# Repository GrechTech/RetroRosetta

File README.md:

# RetroRosetta

Check the Wiki page for more information
https://github.com/GrechTech/RetroRosetta/wiki

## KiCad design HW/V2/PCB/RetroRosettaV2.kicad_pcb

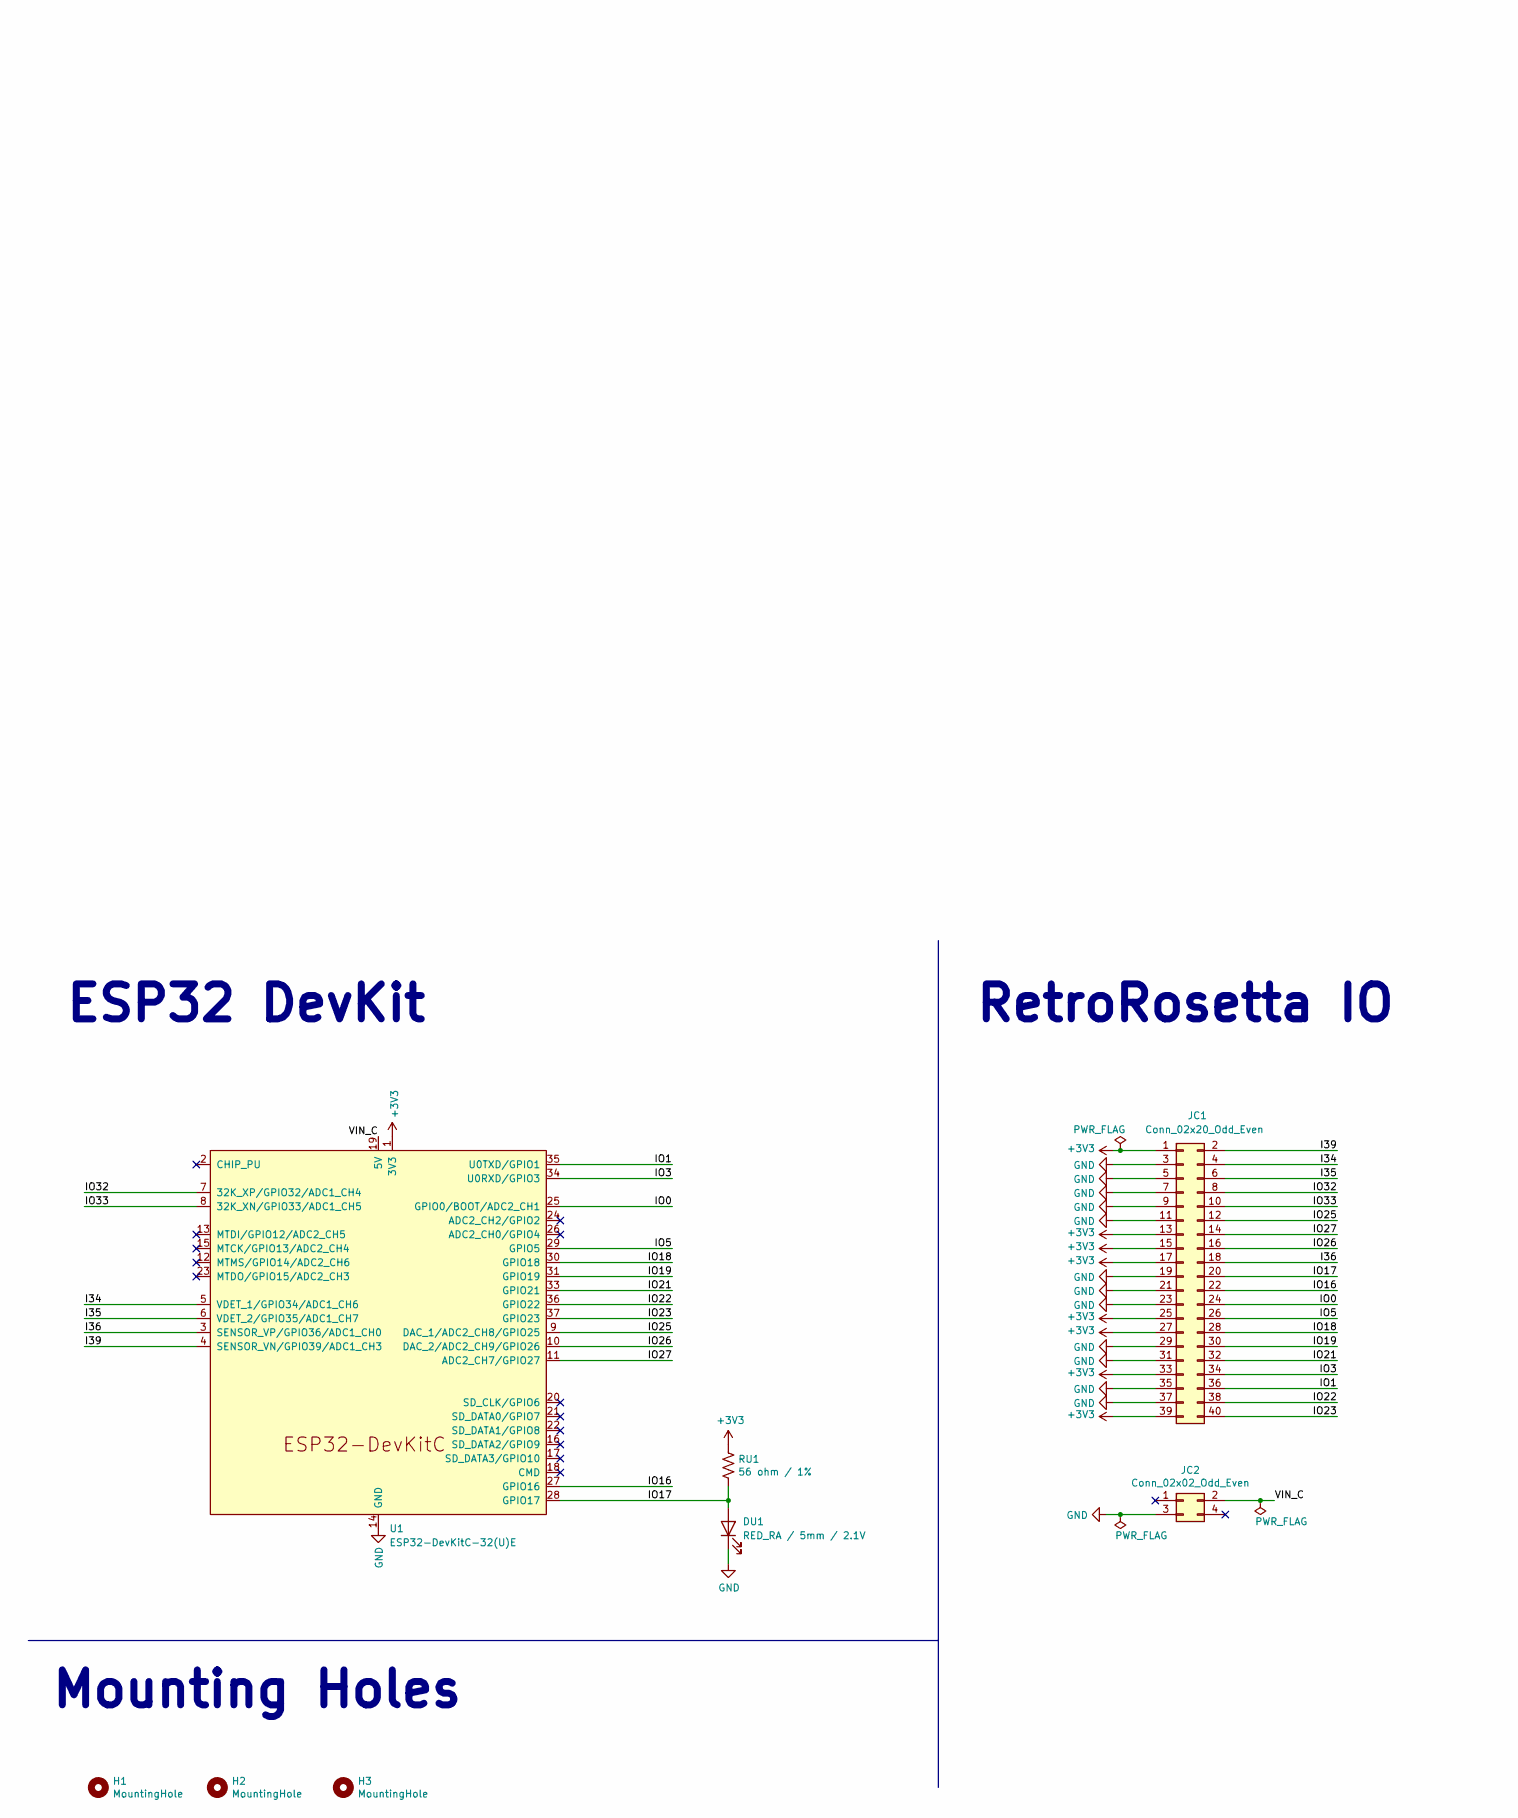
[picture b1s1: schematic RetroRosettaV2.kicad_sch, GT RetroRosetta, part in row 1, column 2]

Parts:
DU1: RED_RA / 5mm / 2.1V; LED_D5.0mm; Manufacturer_Part_Number C503B-RAN-CZ0C0AA2; DigiKey Part Number C503B-RAN-CZ0C0AA2CT-ND
H1, H2, H3: MountingHole; MountingHole_2.2mm_M2; Manufacturer_Part_Number DNP; DigiKey Part Number DNP
JC1: Conn_02x20_Odd_Even; PinHeader_2x20_P2.54mm_Vertical; Manufacturer_Part_Number Male 2.54mm pin header 2x20; DigiKey Part Number Male 2.54mm pin header 2x20
JC2: Conn_02x02_Odd_Even; PinHeader_2x02_P2.54mm_Vertical; Manufacturer_Part_Number Male 2.54mm pin header 2x2; DigiKey Part Number Male 2.54mm pin header 2x2
RU1: 56 ohm / 1%; R_Axial_DIN0204_L3.6mm_D1.6mm_P7.62mm_Horizontal; Manufacturer_Part_Number MFR-25FTE52-56R; DigiKey Part Number 13-MFR-25FTE52-56RCT-ND
U1: ESP32-DevKitC-32(U)E; ESP32-DevKitC; Manufacturer_Part_Number ESP32-DEVKITC-32E; DigiKey Part Number 1965-ESP32-DEVKITC-32E-ND

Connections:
+3V3: JC1.1, JC1.13, JC1.15, JC1.17, JC1.25, JC1.27, JC1.33, JC1.39, RU1.1, U1.1 (3V3)
/I34: JC1.4, U1.5 (VDET_1/GPIO34/ADC1_CH6)
/I35: JC1.6, U1.6 (VDET_2/GPIO35/ADC1_CH7)
/I36: JC1.18, U1.3 (SENSOR_VP/GPIO36/ADC1_CH0)
/I39: JC1.2, U1.4 (SENSOR_VN/GPIO39/ADC1_CH3)
/IO0: JC1.24, U1.25 (GPIO0/BOOT/ADC2_CH1)
/IO1: JC1.36, U1.35 (U0TXD/GPIO1)
/IO3: JC1.34, U1.34 (U0RXD/GPIO3)
/IO5: JC1.26, U1.29 (GPIO5)
/IO16: JC1.22, U1.27 (GPIO16)
/IO17: DU1.2 (A), JC1.20, RU1.2, U1.28 (GPIO17)
/IO18: JC1.28, U1.30 (GPIO18)
/IO19: JC1.30, U1.31 (GPIO19)
/IO21: JC1.32, U1.33 (GPIO21)
/IO22: JC1.38, U1.36 (GPIO22)
/IO23: JC1.40, U1.37 (GPIO23)
/IO25: JC1.12, U1.9 (DAC_1/ADC2_CH8/GPIO25)
/IO26: JC1.16, U1.10 (DAC_2/ADC2_CH9/GPIO26)
/IO27: JC1.14, U1.11 (ADC2_CH7/GPIO27)
/IO32: JC1.8, U1.7 (32K_XP/GPIO32/ADC1_CH4)
/IO33: JC1.10, U1.8 (32K_XN/GPIO33/ADC1_CH5)
/VIN_C: JC2.2, U1.19 (5V)
GND: DU1.1 (K), JC1.3, JC1.5, JC1.7, JC1.9, JC1.11, JC1.19, JC1.21, JC1.23, JC1.29, JC1.31, JC1.35, JC1.37, JC2.3, U1.14 (GND), U1.32 (GND), U1.38 (GND)

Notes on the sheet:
Mounting Holes
ESP32 DevKit
RetroRosetta IO

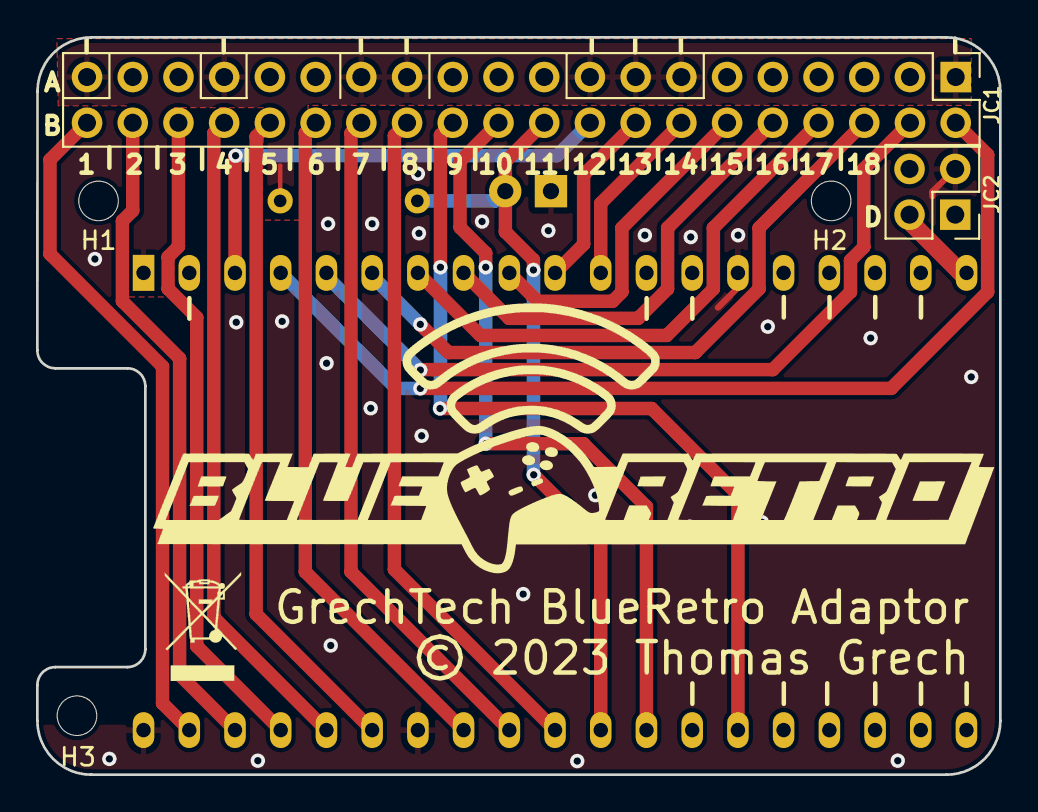
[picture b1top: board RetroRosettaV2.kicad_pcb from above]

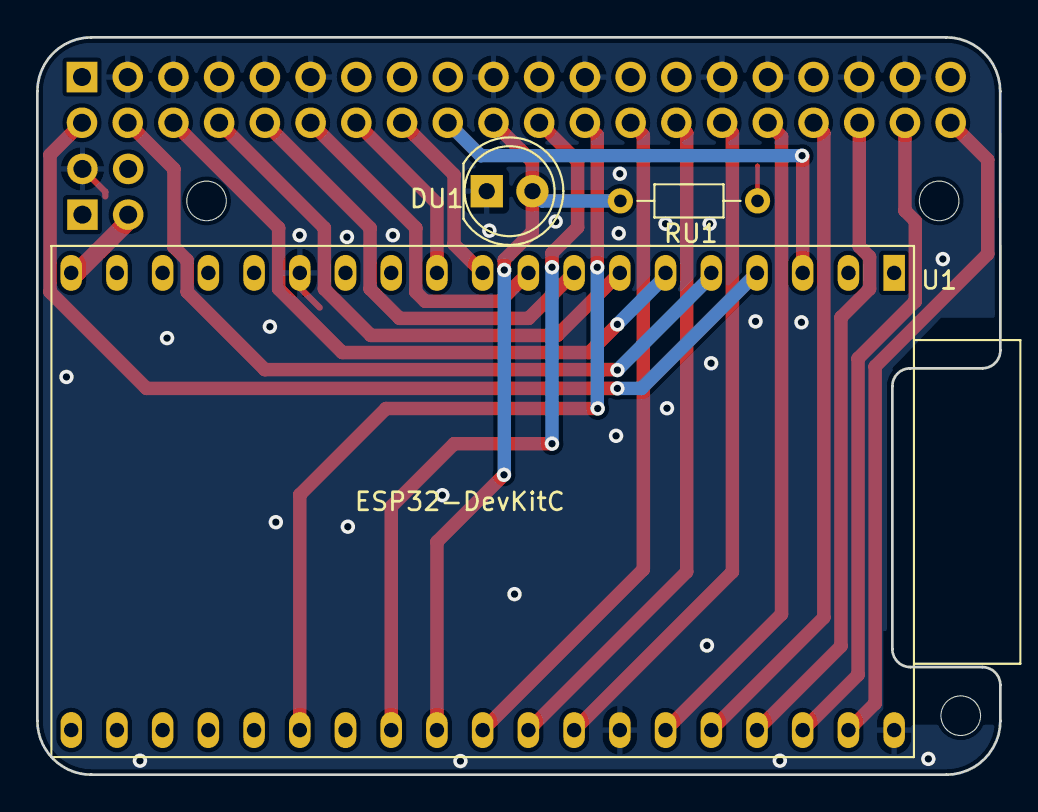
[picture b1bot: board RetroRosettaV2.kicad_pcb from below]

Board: 2 copper layers, 53.5 x 41.0 mm, 8 parts (3 on the bottom side), 23 nets.

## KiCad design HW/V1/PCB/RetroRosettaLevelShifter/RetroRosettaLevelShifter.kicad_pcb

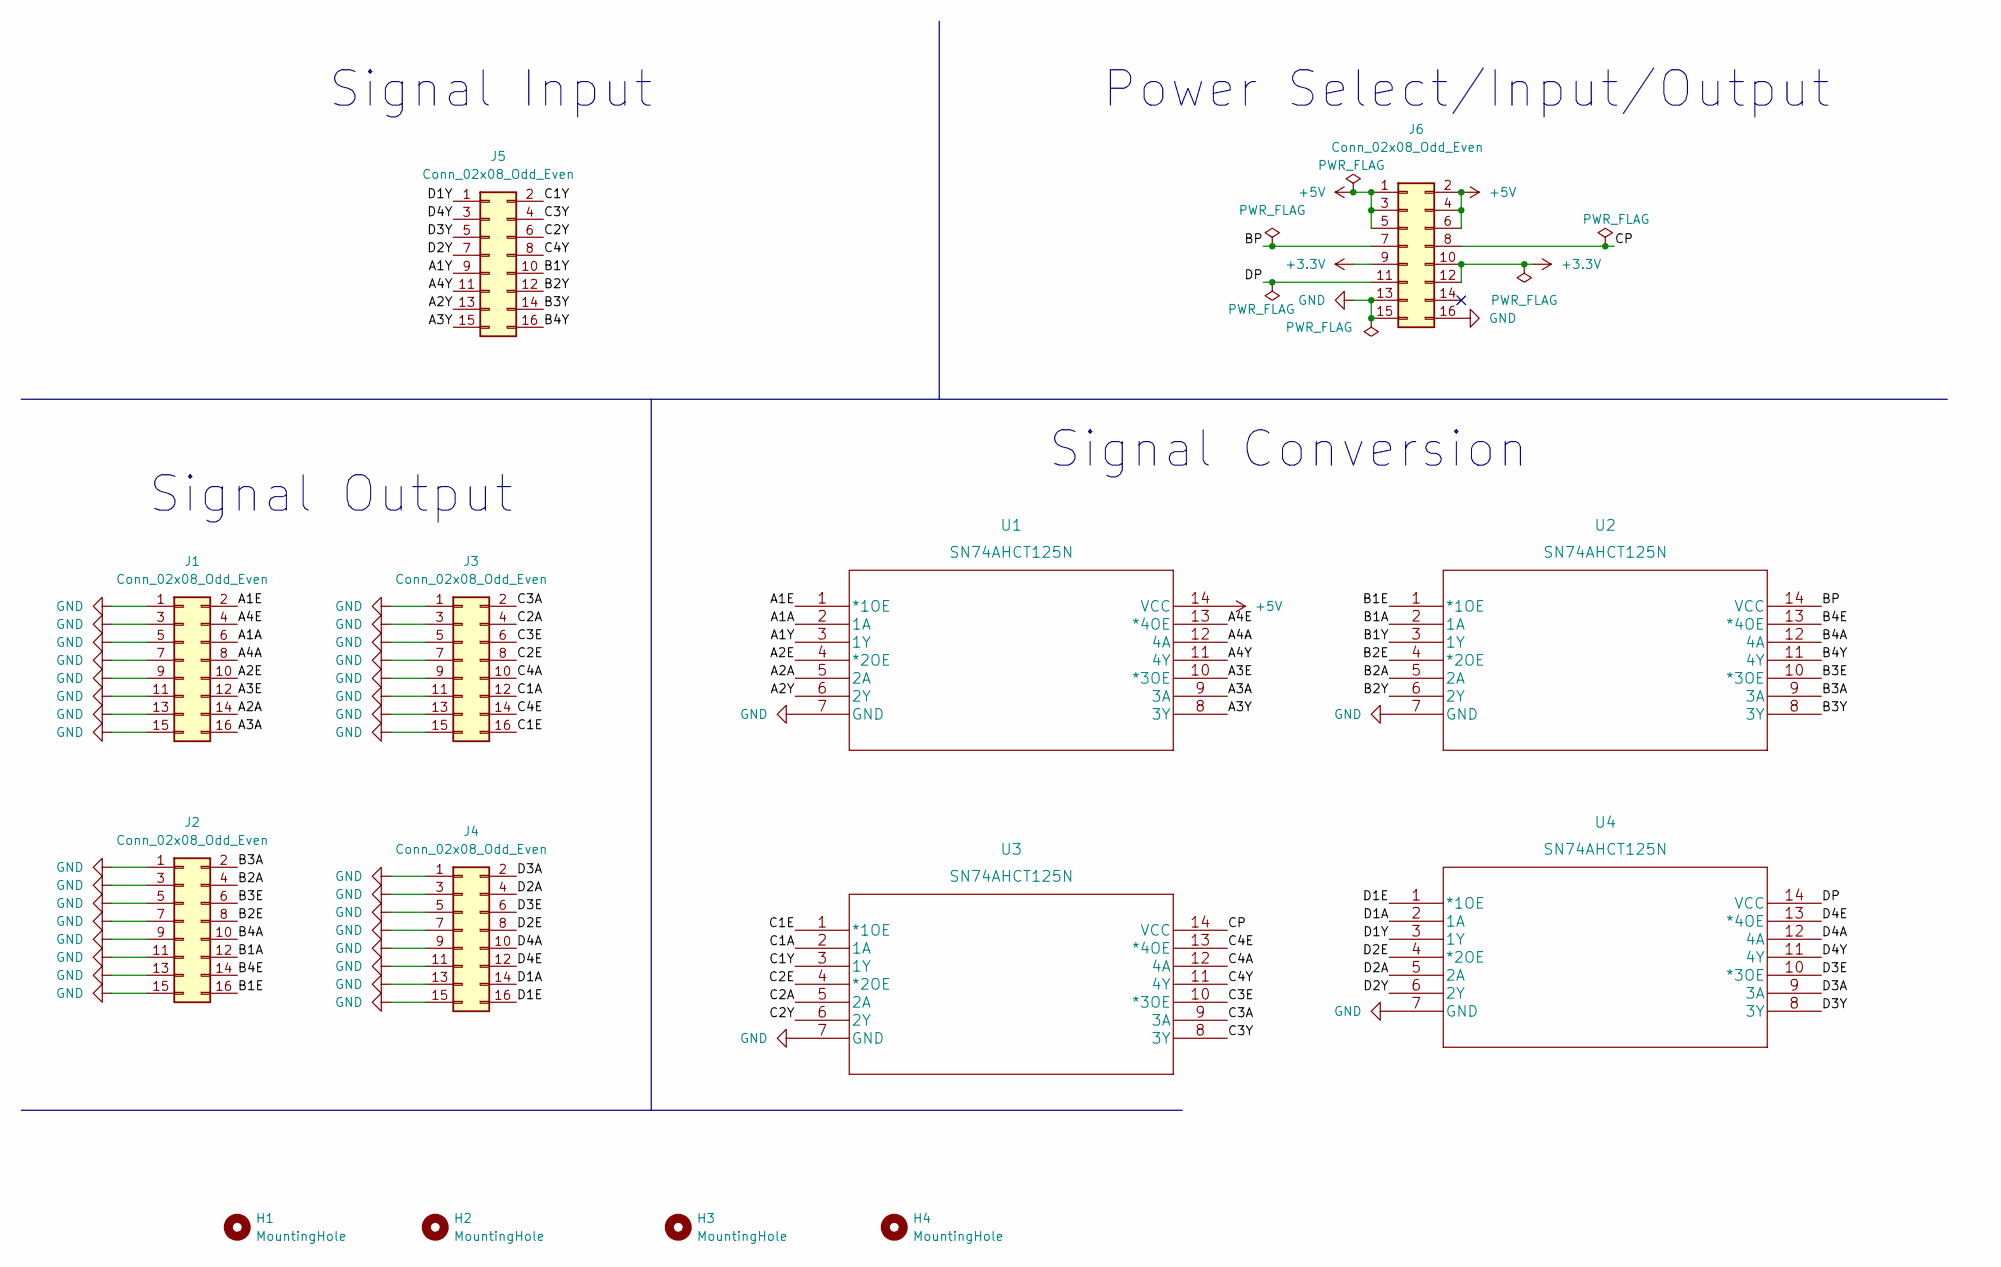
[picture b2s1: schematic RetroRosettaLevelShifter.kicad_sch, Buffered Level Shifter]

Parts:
H1, H2, H3, H4: MountingHole; MountingHole_2.7mm_M2.5
J1, J2, J3, J4, J5, J6: Conn_02x08_Odd_Even; PinHeader_2x08_P2.54mm_Vertical
U1, U2, U3, U4: SN74AHCT125N

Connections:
+3.3V: J6.9, J6.10, J6.12
+5V: J6.1, J6.2, J6.3, J6.4, J6.5, J6.6, U1.14 (VCC)
/A1A: J1.6, U1.2 (1A)
/A1E: J1.2, U1.1 (*1OE)
/A1Y: J5.9, U1.3 (1Y)
/A2A: J1.14, U1.5 (2A)
/A2E: J1.10, U1.4 (*2OE)
/A2Y: J5.13, U1.6 (2Y)
/A3A: J1.16, U1.9 (3A)
/A3E: J1.12, U1.10 (*3OE)
/A3Y: J5.15, U1.8 (3Y)
/A4A: J1.8, U1.12 (4A)
/A4E: J1.4, U1.13 (*4OE)
/A4Y: J5.11, U1.11 (4Y)
/B1A: J2.12, U2.2 (1A)
/B1E: J2.16, U2.1 (*1OE)
/B1Y: J5.10, U2.3 (1Y)
/B2A: J2.4, U2.5 (2A)
/B2E: J2.8, U2.4 (*2OE)
/B2Y: J5.12, U2.6 (2Y)
/B3A: J2.2, U2.9 (3A)
/B3E: J2.6, U2.10 (*3OE)
/B3Y: J5.14, U2.8 (3Y)
/B4A: J2.10, U2.12 (4A)
/B4E: J2.14, U2.13 (*4OE)
/B4Y: J5.16, U2.11 (4Y)
/BP: J6.7, U2.14 (VCC)
/C1A: J3.12, U3.2 (1A)
/C1E: J3.16, U3.1 (*1OE)
/C1Y: J5.2, U3.3 (1Y)
/C2A: J3.4, U3.5 (2A)
/C2E: J3.8, U3.4 (*2OE)
/C2Y: J5.6, U3.6 (2Y)
/C3A: J3.2, U3.9 (3A)
/C3E: J3.6, U3.10 (*3OE)
/C3Y: J5.4, U3.8 (3Y)
/C4A: J3.10, U3.12 (4A)
/C4E: J3.14, U3.13 (*4OE)
/C4Y: J5.8, U3.11 (4Y)
/CP: J6.8, U3.14 (VCC)
/D1A: J4.14, U4.2 (1A)
/D1E: J4.16, U4.1 (*1OE)
/D1Y: J5.1, U4.3 (1Y)
/D2A: J4.4, U4.5 (2A)
/D2E: J4.8, U4.4 (*2OE)
/D2Y: J5.7, U4.6 (2Y)
/D3A: J4.2, U4.9 (3A)
/D3E: J4.6, U4.10 (*3OE)
/D3Y: J5.5, U4.8 (3Y)
/D4A: J4.10, U4.12 (4A)
/D4E: J4.12, U4.13 (*4OE)
/D4Y: J5.3, U4.11 (4Y)
/DP: J6.11, U4.14 (VCC)
GND: J1.1, J1.3, J1.5, J1.7, J1.9, J1.11, J1.13, J1.15, J2.1, J2.3, J2.5, J2.7, J2.9, J2.11, J2.13, J2.15, J3.1, J3.3, J3.5, J3.7, J3.9, J3.11, J3.13, J3.15, J4.1, J4.3, J4.5, J4.7, J4.9, J4.11, J4.13, J4.15, J6.13, J6.15, J6.16, U1.7 (GND), U2.7 (GND), U3.7 (GND), U4.7 (GND)

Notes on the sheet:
Power Select/Input/Output
Signal Conversion
Signal Input
Signal Output

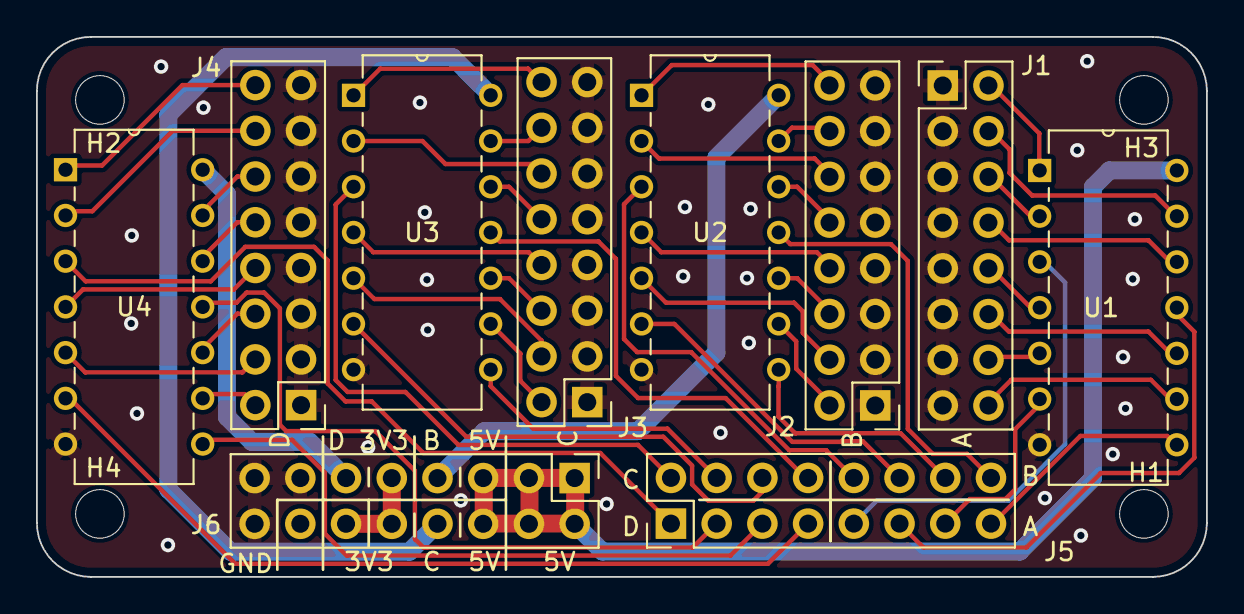
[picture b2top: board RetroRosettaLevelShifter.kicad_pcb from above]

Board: 2 copper layers, 65.0 x 30.0 mm, 14 parts (0 on the bottom side), 54 nets.

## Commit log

2022-08-09 Cable setup guides batch 1
    Cable guides for: N64, Gamecube, Dreamcast, PS1/PS2
    Details the construction of the cables, and the connections of the cables and accompanying jumper caps to the RetroRosetta PCB
2022-08-23 Clean
2023-01-31 Create Case2
2023-08-09 Create Open Source Hardware List
2023-12-24 RR V2 upload
2023-12-26 Migrate documentation for V2
2023-12-26 Rename files

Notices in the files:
HW/V2/PCB/RetroRosettaV2.kicad_pcb:
This PCB design is licensed under MIT Open Source License.
© 2023 Thomas Grech
HW/V2/PCB/RetroRosettaV2.kicad_sch:
For BlueRetro ESP32 Universal FW ©2020 Jacques Gagnon
